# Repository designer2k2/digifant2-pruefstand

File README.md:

# Digifant-2 Prüfstand

Hardware for a fully-automated test bench for the VW Golf 1 Cabrio **Digifant-2** ECU:
signal simulator + capture front-end, driven by a Raspberry Pi Pico 2, with a
high-side load switch so the bench can cold-boot the ECU and cut power on
overcurrent. Scope here is the **Signal-Simulator + Erfassungseinheit** only — the
EPROM emulator is a separate future board.

The schematic is generated from Python with
[circuit-synth](https://github.com/circuit-synth/circuit-synth); the PCB is placed
and autorouted headless (`pcbnew` + Freerouting).

**[`firmware/OPERATION.md`](firmware/OPERATION.md) — how to operate the
bench: display and buttons, PC control and scripting, reading the
measurements.**

**[`BRINGUP.md`](BRINGUP.md) — step-by-step first power-on checklist, tools
needed, and the open questions to settle on the bench.**

**[`DESIGN.md`](DESIGN.md) — what every block does, part-selection rationale, the
GPIO / I²C / VW-harness maps.** [`USE_CASES.md`](USE_CASES.md) traces every real
bench use case through the schematic to concrete numbers (voltage/current/timing
headroom) — a requirements/test matrix for the hardware, and where the AD9833
decoupling-cap gap turned up before it got fixed.

## Layout

| path | what |
|------|------|
| `digifant2_pruefstand.py` | the circuit — one `@circuit` function, flat single sheet |
| `gen_custom_symbols.py` | builds `kicad-symbols/Custom_Digifant2.kicad_sym` (INA226, AD9833, 2N7002, DPAK P-FET, VW connector — pinouts verified against datasheets) |
| `gen_project.py` | `python3 gen_project.py <name>` → full KiCad project + netlist + lib tables, runs ERC/DRC via `kicad-cli`, auto-applies no-connect flags |
| `place_and_route.py` | `pcbnew` functional-zone placement → Specctra DSN → Freerouting → SES import (run inside the KiCad flatpak; `java` runs outside it) |
| `add_nc_flags.py` | stamps `no_connect` flags from an ERC report (circuit-synth has no NC API) |
| `fix_layout.py` | post-route layout surgery (real netclasses, GND/Kelvin re-routing) — see the header comment for the 2-phase, 2-process invocation it needs |
| `reroute_missing.py` | re-exports a Specctra DSN from a partially-ripped-up board so Freerouting only has to fill the reopened ratsnest |
| [`firmware/`](firmware/README.md) | Pico firmware (Pico SDK, C): USB serial command protocol, build/flash instructions, what's implemented vs. stubbed |
| `host/bench.py` | PC-side client for the firmware protocol: interactive prompt, one-shot CLI, or importable `Bench` class; `host/examples/` has a scripted rpm sweep |
| `board/` | the current KiCad project (144×150 mm, 2-layer, 4× M3 corner holes, isolated OLED + USB clearance zones) |
| [`board/bom_output/bom.html`](board/bom_output/bom.html) | interactive BOM ([InteractiveHtmlBom](https://github.com/openscopeproject/InteractiveHtmlBom)) — click a part to highlight it on the board, no KiCad needed |
| [`BOM.md`](BOM.md) | Mouser sourcing: part numbers for every line item, with confidence notes — 6 of 30 need manual confirmation, see the file |
| [`mouser_cart.csv`](mouser_cart.csv) | only the Mouser-verified part numbers, ready to paste into Mouser's bulk order tool |
| [`JLCPCB_ASSEMBLY.md`](JLCPCB_ASSEMBLY.md) | hybrid plan: JLCPCB machine-places the SMD parts, you hand-solder THT + 4 unconfirmed SMD parts — read this before submitting |
| [`jlcpcb_bom.csv`](jlcpcb_bom.csv) / [`jlcpcb_cpl.csv`](jlcpcb_cpl.csv) | JLCPCB SMT-assembly BOM + pick-and-place, 42 of 46 SMD parts (real positions from `board/`, real LCSC part numbers) |
| `UPSTREAM_BUGS.md` | circuit-synth bugs found, drafted for upstream filing |
| `kicad-symbols/`, `kicad-footprints/` | libraries — custom/community committed, stock via `./fetch_libs.sh` |
| `.github/workflows/` | CI: firmware build + tests, spell check, KiCad ERC/DRC, firmware releases (see below) |

## Build

```sh
./fetch_libs.sh                        # one-time: pull stock KiCad 9.0 libs
python3 gen_custom_symbols.py          # if the custom symbols changed
python3 gen_project.py digifant2_pruefstand_cs_v1
```

Placement + routing needs KiCad's `pcbnew` Python API (KiCad ≥ 10) and a
non-headless JRE for Freerouting — see the header of `place_and_route.py`.

## Status

Schematic ERC-clean; VW harness pinout verified against the cabby-info.com
Digifant II reference and the user's own hands-on HiL notes (see `DESIGN.md`).
Board placed + autorouted (144 × 150 mm, 2-layer, 4 × M3 holes, isolated OLED + USB
clearance zones), real Power/Gnd netclasses, GND re-routed as one connected net
(was 4 islands), dedicated Kelvin sense traces for both shunts. The tight
U1/U3/RS1/RS2 pocket (2 shorting_items, 2 clearance, 5 tracks_crossing left by
the scripted Kelvin routing) was cleaned up by hand in KiCad's interactive
router, and a B.Cu GND pour was added. Added the two AD9833 decoupling caps
(C7, C8), fully routed. Fixed RS2 (idle-valve shunt) to be truly in series
with the ECU's VW-23 driver instead of a parallel path to GND that was
corrupting the current reading — this reopened one small pocket at U3 pin 9
(2 `shorting_items`, confined to that one spot after extensive
hand-routing/Freerouting attempts, same class of residual as the historical
U1/U3/RS1/RS2 items). Gave the AD9833 knock output a defined path out
(TP1/TP2 test points for VW-4/VW-5) instead of a dead end. Added 12 more
THT scope-probe test points (TP3–TP14, real drilled holes — an earlier pass
used bare SMD pads and put 10 of them physically underneath the Pico module,
both corrected) on the main GPIO signals, both buses, and both 12 V rails.
Found and fixed a real bug along the way: footprints cloned via
`pcbnew.FOOTPRINT(template)` inherit the template's UUID unless you
explicitly reset it, which had corrupted DRC's item-identity tracking for
every cloned part this session (C7/C8 and all of TP1–TP14) — several
"violations" turned out to be real defects reported against the wrong
footprint. See DESIGN.md's "Known open points" for details if you script
further additions. Remaining warnings are cosmetic (silkscreen overlap,
lib_footprint_mismatch, and one starved_thermal note on a single Pico GND
pad with only 1 pour spoke instead of 2 — connected fine, just a slightly
weaker thermal/mechanical joint). Thermal copper for D1/Q2 still optional to
add by hand. Added a 12×16 perfboard-style proto area (PROTO1, isolated THT
pads on 0.1″ pitch) in the empty space bottom-right of J0. Checked the whole
board against JLCPCB's published fab minimums (trace/spacing, via/hole sizes,
hole-to-hole, copper-to-edge, board thickness) — everything copper- and
hole-related had 1.5×–14× margin already. The one real miss was silkscreen:
KiCad's default 0.1mm line width and 0.8mm text height are both below
JLCPCB's stated minimums (0.15mm / 1.0mm), risking thin/dropped silkscreen.
Bumped the project defaults and widened/enlarged every existing silkscreen
line and text item on the board to meet those minimums.

Checked +3V3 for adequate trace width (it's on the thinnest `Default`
netclass, 0.2mm, despite feeding ~15 chips) — worked out the real numbers
(thermal capacity ~0.77A at 10°C rise, worst-case drop a few mV) and it's
fine as-is; not worth the rerouting risk in this densely-packed board.
Checked decoupling instead: per each part's own datasheet, U1 and U3 (the
two INA226 current-sense amps) had no bypass cap at all, unlike U2/U4 which
already have theirs (C6, C2/C7/C8). Added C9 (U1) and C10 (U3), 100nF 0805,
tapped directly off the existing +3V3 B.Cu trunk and the GND pour a few mm
south of the packed U1/U3/RS1/RS2 pocket (no room to place them right at the
pins) — verified DRC-clean (the only residuals are the same
new-copper-vs-stale-zone-fill noise that clears on a zone refill, same as
after the TP resort). U6/U7/U8 (the sensor-disconnect analog switches) are
still without a bypass cap; lower priority since they're not
noise-sensitive, but could use the same treatment.

Added the thermal copper for D1/Q2 that was flagged as a real (not
cosmetic) risk in USE_CASES.md — D1 dissipates ~1.25W at sustained ~2.5A
with no thermal relief otherwise. Both pours verified electrically
connected to their pads (not just overlapping) and DRC-clean. Q2's is
small since there's almost no open board space around its DPAK tab; D1's
is generous since F1/RS1 (same nets, either side) leave a wide open
corridor.

**All 14 test points (TP1–TP14) are now fully routed** — the user hand-routed
7 of the 10 remaining GPIO test points after the resort (TP3, TP10, TP11,
TP4, TP12, TP5, TP6); the last 3 (TP9, TP8, TP7 — all on U5's east side, the
tightest part of the board) were routed with a grid-based pathfinder (A* over
a 0.1mm grid, spatial-bucket-indexed for speed) purpose-built for this corridor
after several rounds of manual/heuristic routing kept snagging on real
obstacles: the Pico's own pin column has no gap wide enough for a second
trace anywhere along its length (confirmed by direct probing — routed escape
stubs from other GPIOs fill in what would otherwise be a 0.49mm theoretical
gap between pin pads), so both TP8 and TP9 had to detour around the *south*
end of the Pico footprint entirely, and — since that detour corridor is
itself only wide enough for one trace at a time — needed genuinely different
physical crossing points, not just parallel lanes. Verified via real
`kicad-cli pcb drc`, not just the pathfinder's own clearance model (which
undercounted real collisions during development in two ways worth noting for
next time: it modeled non-circular pads by their half-width instead of their
half-diagonal, and it didn't check hole-to-hole spacing against a net's own
via near its own pad — both are now fixed in the approach, see `DESIGN.md`).
GND zone refilled after all of the above (TP9/TP8 routing, C9/C10, D1/Q2
thermal pours) — DRC dropped from 136 to 101 violations, all pre-existing
cosmetic categories plus the one known `starved_thermal` note, zero
clearance/short/crossing issues. (The "whole-board refill introduces ~115
spurious violations" finding earlier this session was a testing artifact —
running `kicad-cli` against a bare copy of the `.kicad_pcb` without its
paired `.kicad_pro` silently falls back to stricter default netclass rules;
with the project file present, the refill is clean.)

Trimmed the board from 144×169mm to 144×150mm — the bottom 19mm was
completely empty (bare GND pour, nothing below PROTO1/J3 until the old
mounting holes). H3/H4 moved up to keep the same 4.5mm hole-to-edge margin
as H1/H2; DRC stayed clean (99 violations, same pre-existing cosmetic set).

Added functional silkscreen labels next to J0 (the VW harness connector) and
every test point, instead of leaving bare unlabeled pads. J0 gets each pin's
real VW harness number (VW-2, VW-9, ... or GND / +12V SW) in the clear strip
just outside its footprint. The TPs already had descriptive text (e.g.
`GP2_CRANK`) sitting on them from earlier in the session — turned out it was
on **F.Fab**, a documentation-only layer that doesn't actually get printed on
the physical board, so none of it was ever going to be visible with a probe
in hand. Moved it to F.SilkS and shortened the long ones (e.g.
`GP6_THROTTLE_IDLE_SW` → `IDLE SW`) since the west-margin TP column only has
about 10mm of clearance between the board edge and the Pico's pin column —
the original full-length strings would have run off the board edge once
actually rendered as real silkscreen (checked via real bounding-box widths,
not by eye). This did add some new `silk_overlap` hits — mostly TP labels
sitting close to the Pico module's own tiny per-pin silkscreen text in that
same tight corridor — all cosmetic, same accepted category as the rest of
this board's silkscreen warnings, verified via DRC to introduce zero
clearance/short/crossing issues.

Added fab-identification text on the back silkscreen (B.SilkS, previously
completely empty — no back components, nothing on that layer at all):
project name, revision, date, and designer, so a bare board can still be
identified later. Set via the board's title block (`${TITLE}`,
`${REVISION}`, `${ISSUE_DATE}`, `${COMPANY}`) rather than hardcoded text, so
updating the revision/date for a future respin is a one-place edit in
KiCad's Page Settings, not a silkscreen re-edit. Verified the variables
resolve correctly (checked the exported SVG's embedded text, since this
sandbox can't render the actual glyphs) and confirmed zero new DRC
violations. Not yet fabbed.

## Continuous integration

Every push and pull request runs on GitHub Actions:

| Workflow | What it checks |
|---|---|
| **CI** (`ci.yml`) | Builds the firmware with Pico SDK 2.1.1, warnings as errors, and uploads `pruefstand.uf2` as a build artifact. Runs `firmware/test/run_all.sh`: all PC unit tests, the command parser, `host/bench.py` over a virtual serial port, and the crank PIO program in an emulator. |
| | Spell check with [codespell](https://github.com/codespell-project/codespell) over code, comments and docs (`.codespellrc`). |
| **Board** (`board.yml`, only when `board/` changes) | KiCad 10 ERC, and DRC with schematic parity. Fails on errors (unconnected nets, clearance, shorts); the known cosmetic warnings are only reported. Full reports are attached to the run. |

Before opening a pull request, the same checks run locally with
`firmware/test/run_all.sh` (after a firmware build) and `codespell`.

**Firmware releases:** bump `FW_VERSION` in `firmware/src/cmd.h`, commit, then
push a matching tag, e.g. `git tag fw-v0.9.0 && git push origin fw-v0.9.0`. CI
checks the tag against `FW_VERSION`, runs everything above, and publishes a
GitHub Release with `pruefstand-<version>.uf2` to download and flash.

## License

MIT (see `LICENSE`) for everything authored here — scripts, custom symbols, the
board design. Bundled third-party files (the Raspberry Pi Pico symbol/footprint
from [ncarandini/KiCad-RP-Pico](https://github.com/ncarandini/KiCad-RP-Pico),
CC-BY-SA-4.0) keep their own licenses — see `NOTICE`.

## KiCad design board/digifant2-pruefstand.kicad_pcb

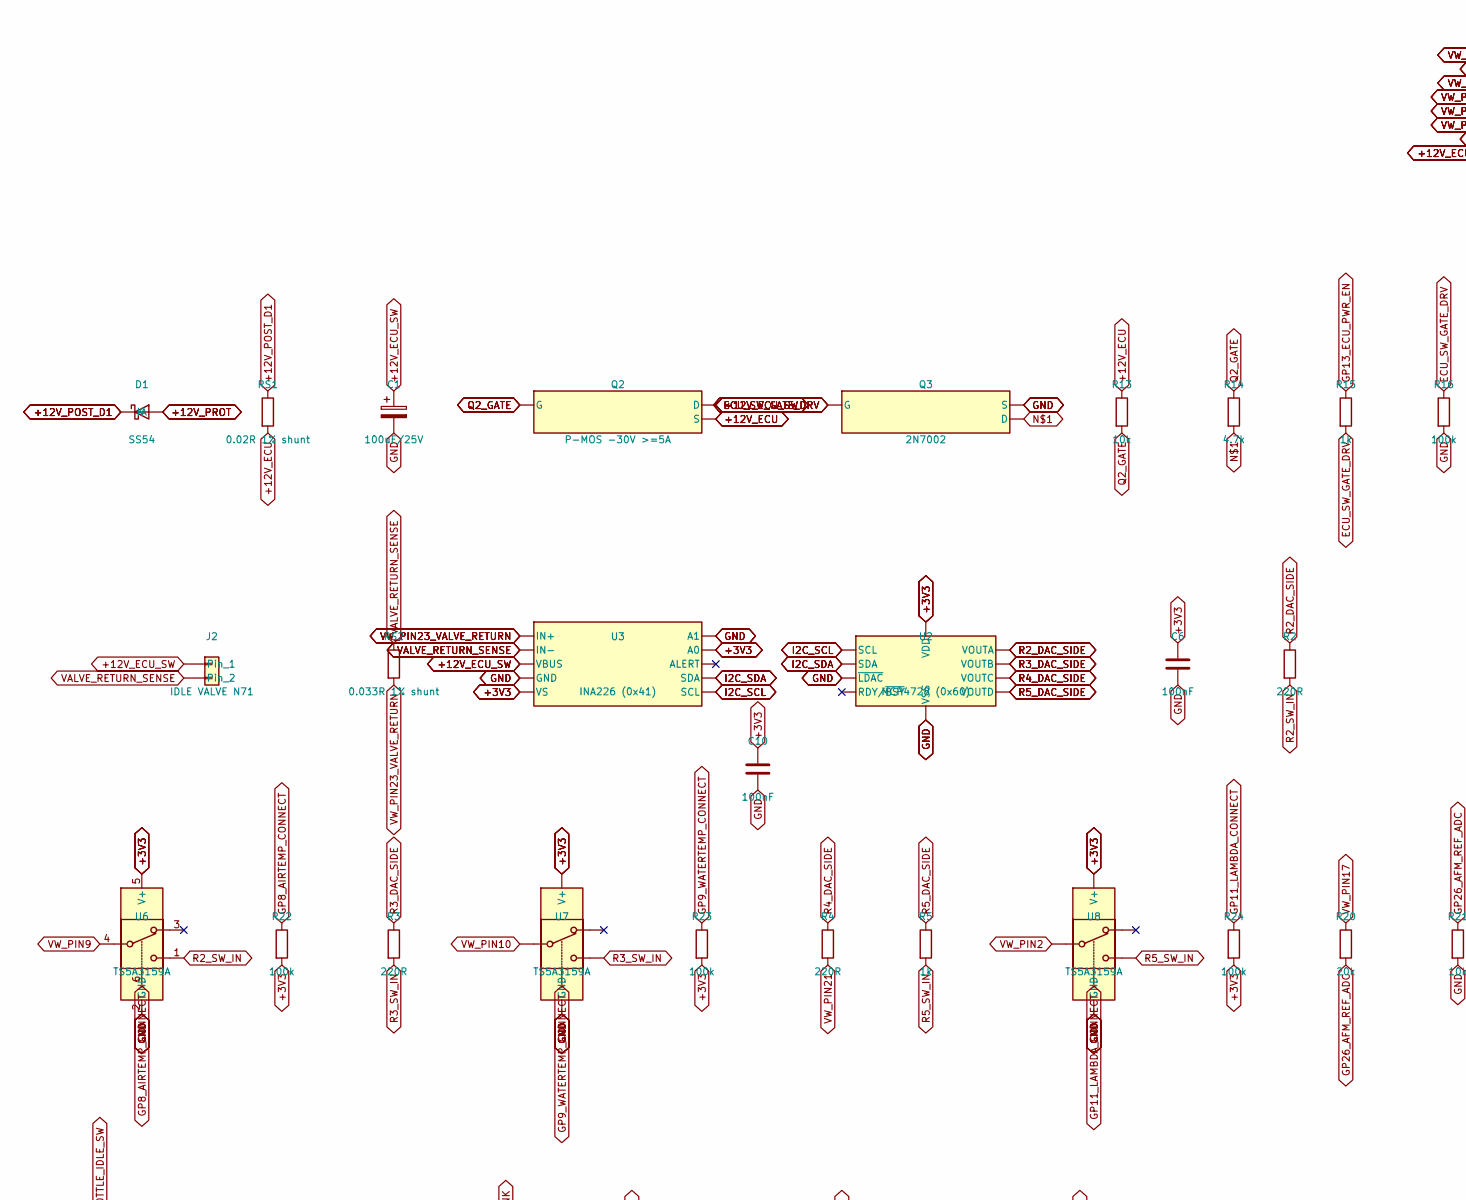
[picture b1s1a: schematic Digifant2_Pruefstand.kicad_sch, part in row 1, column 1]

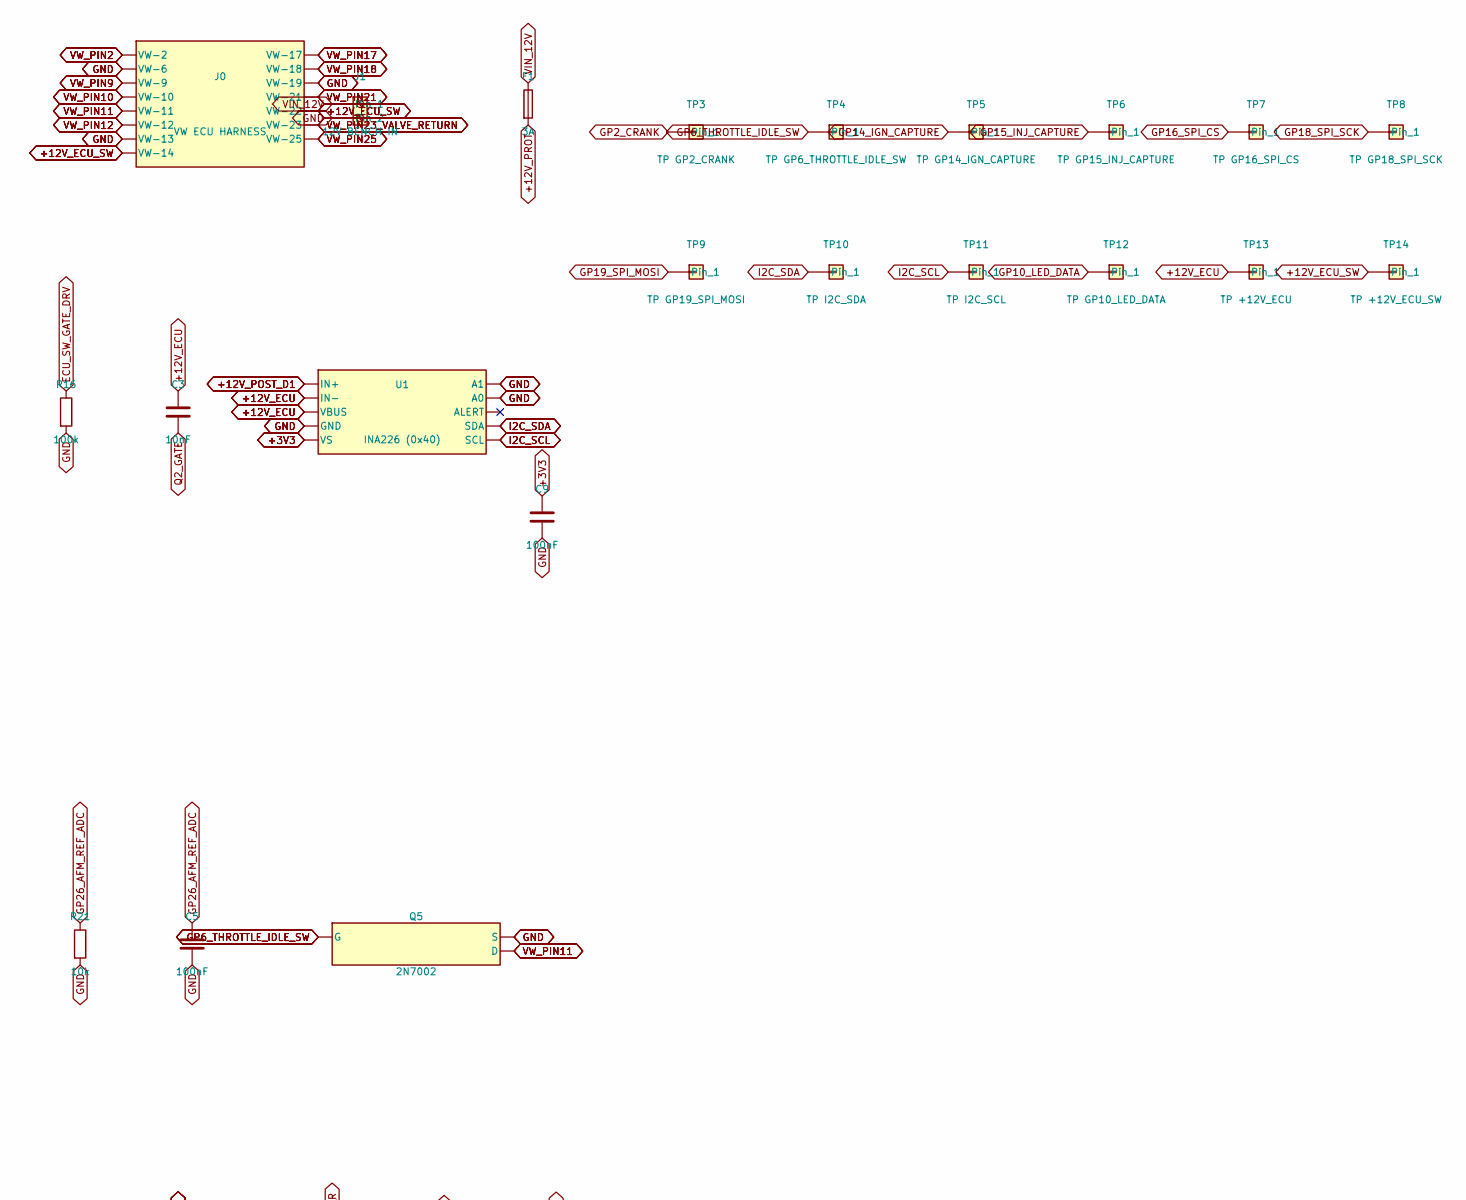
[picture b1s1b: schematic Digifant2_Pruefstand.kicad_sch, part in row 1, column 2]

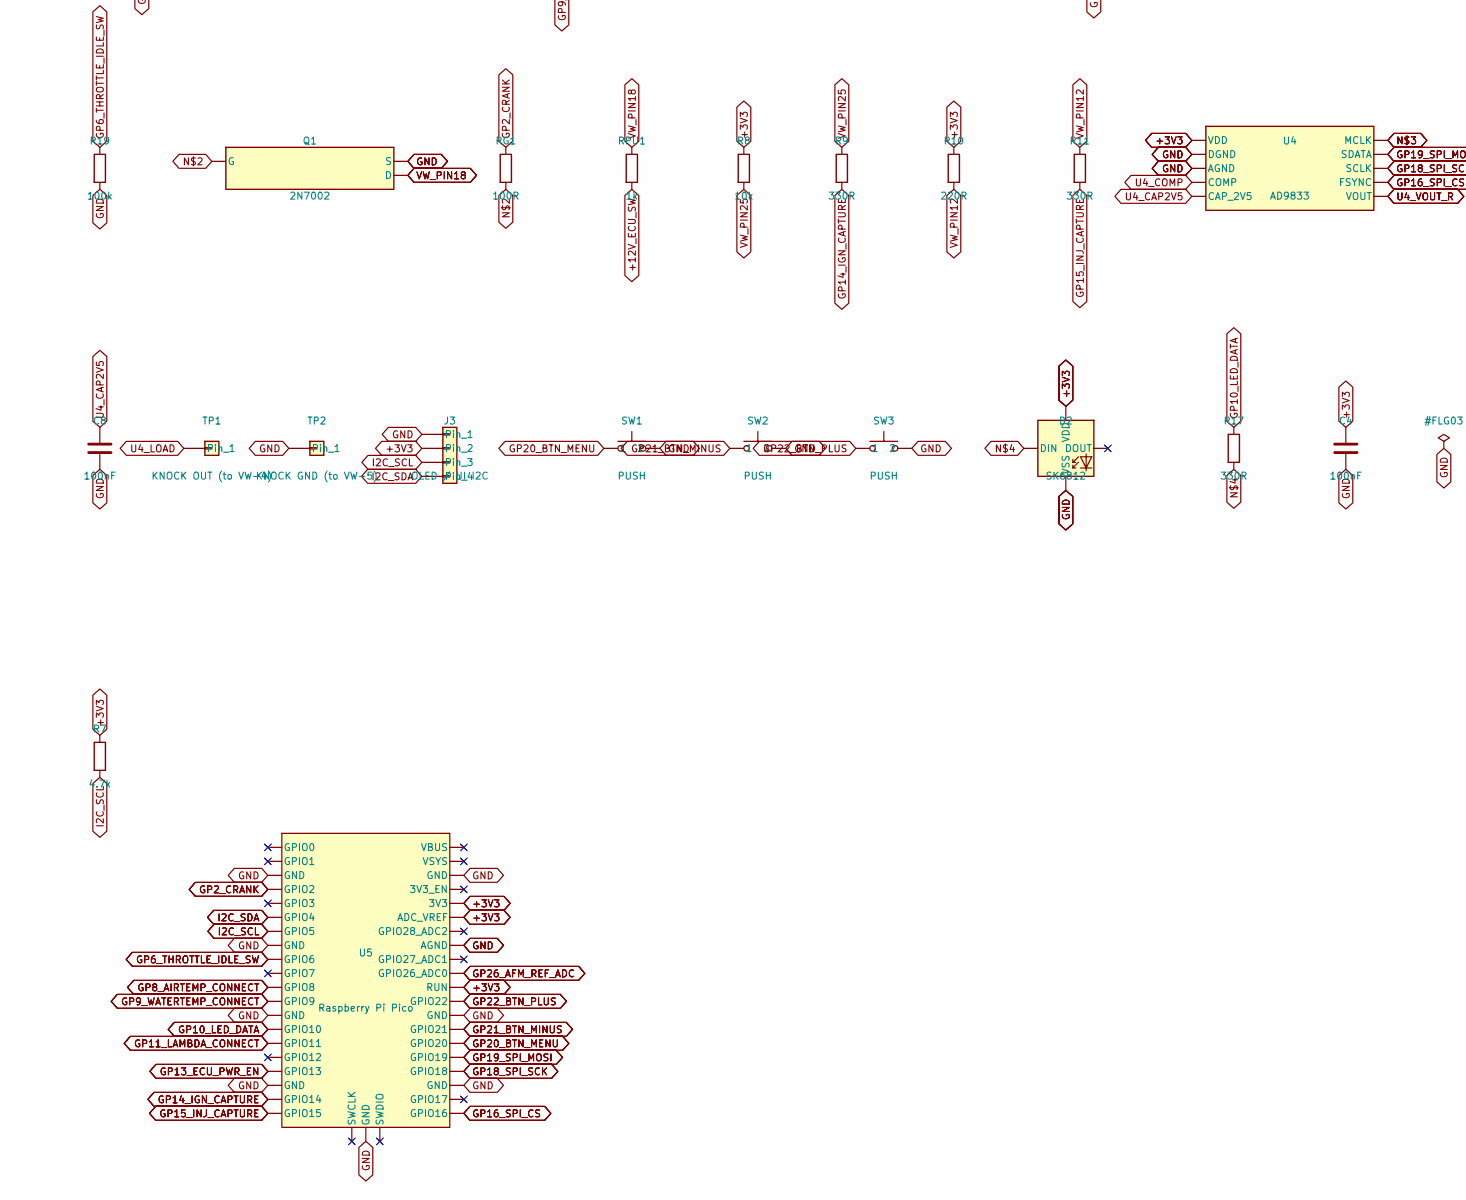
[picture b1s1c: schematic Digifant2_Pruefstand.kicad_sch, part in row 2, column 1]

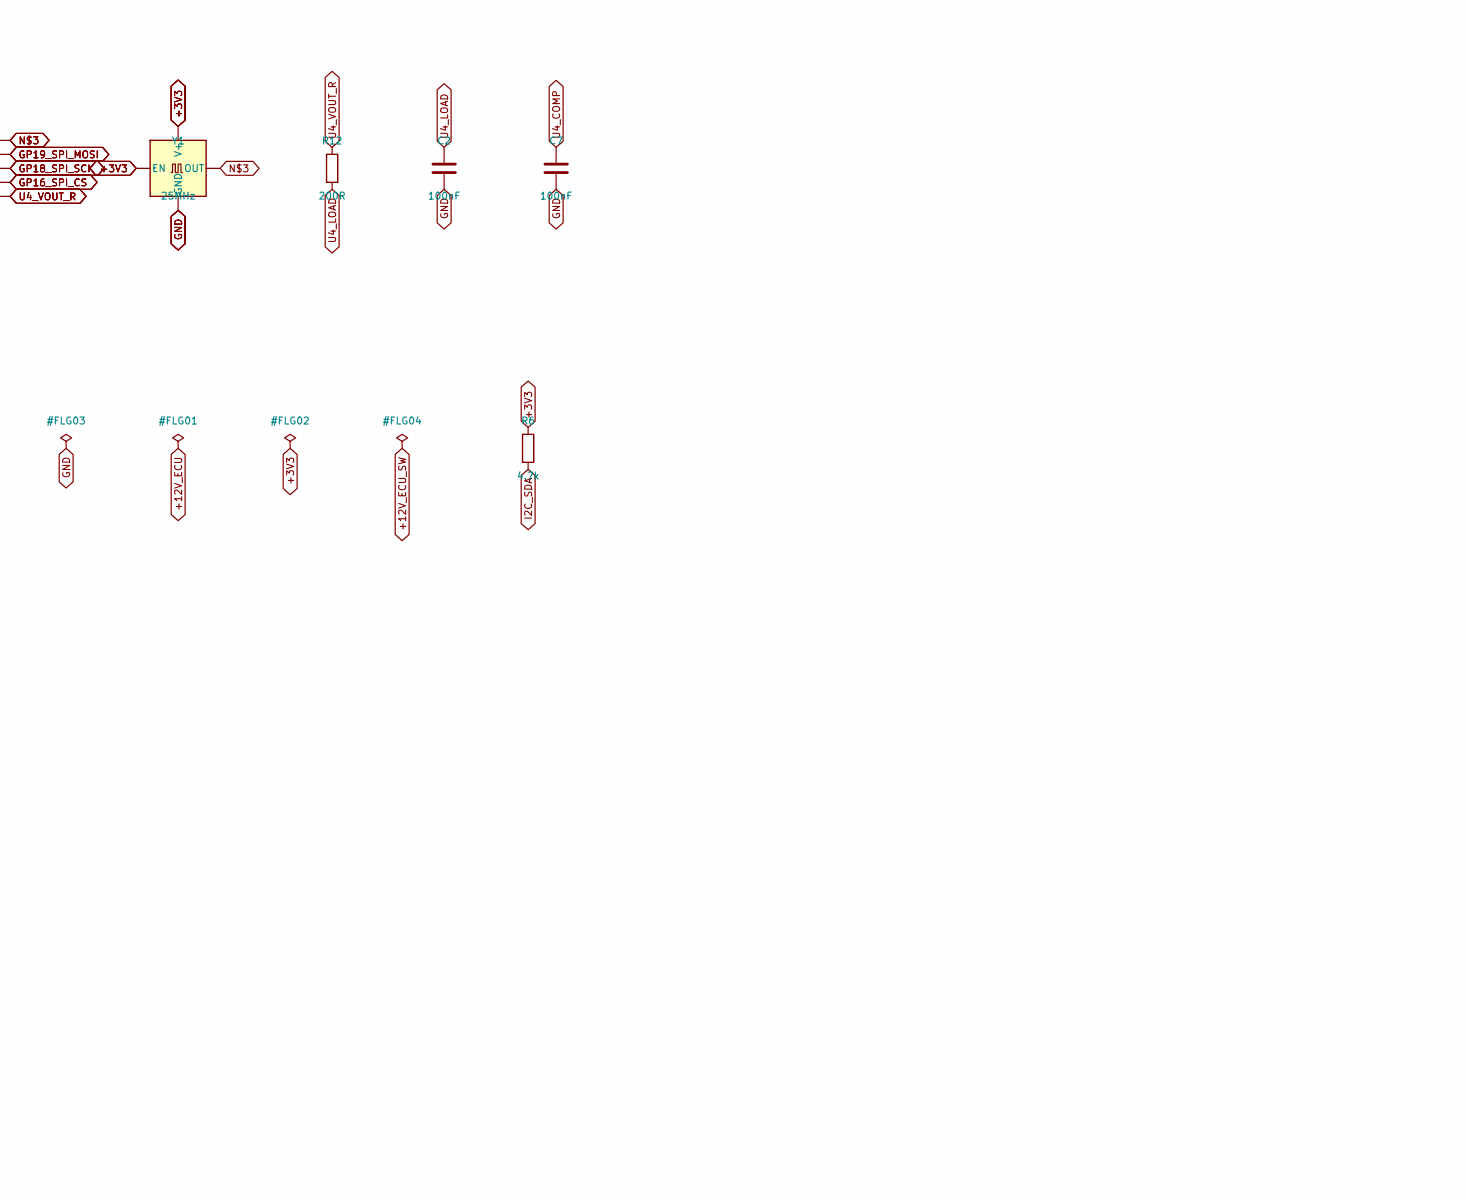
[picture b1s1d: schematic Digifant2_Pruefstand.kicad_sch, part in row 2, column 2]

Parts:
C1: 100uF/25V; CP_Radial_D8.0mm_P3.50mm
C2, C4, C5, C6, C7, C8, C9, C10: 100nF; C_0805_2012Metric
C3: 10nF; C_0805_2012Metric
D1: SS54; D_SMC
D2: SK6812; LED_SK6812_PLCC4_5.0x5.0mm_P3.2mm
F1: 3A; Fuse_1206_3216Metric
J0: VW ECU HARNESS; TerminalBlock_MaiXu_MX126-5.0-15P_1x15_P5.00mm
J1: 12V BENCH IN; TerminalBlock_bornier-2_P5.08mm
J2: IDLE VALVE N71; JST_XH_B2B-XH-A_1x02_P2.50mm_Vertical
J3: OLED / UI I2C; PinHeader_1x04_P2.54mm_Vertical
Q1, Q3, Q5: 2N7002; SOT-23
Q2: P-MOS -30V >=5A; TO-252-2
R2, R3, R4, R10: 220R; R_0805_2012Metric
R5, R15: 1k; R_0805_2012Metric
R6, R7, R14: 4.7k; R_0805_2012Metric
R8, R13, R21: 10k; R_0805_2012Metric
R9, R11, R17: 330R; R_0805_2012Metric
R12: 200R; R_0805_2012Metric
R16, R19, R22, R23, R24: 100k; R_0805_2012Metric
R20: 20k; R_0805_2012Metric
RG1: 100R; R_0805_2012Metric
RPU1: 1k; R_0805_2012Metric
RS1: 0.02R 1% shunt; R_2512_6332Metric
RS2: 0.033R 1% shunt; R_2512_6332Metric
SW1, SW2, SW3: PUSH; SW_PUSH_6mm
TP1: KNOCK OUT (to VW-4); TestPoint_THTPad_D1.5mm_Drill0.7mm
TP2: KNOCK GND (to VW-5); TestPoint_THTPad_D1.5mm_Drill0.7mm
TP3: TP GP2_CRANK; TestPoint_THTPad_D1.5mm_Drill0.7mm
TP4: TP GP6_THROTTLE_IDLE_SW; TestPoint_THTPad_D1.5mm_Drill0.7mm
TP5: TP GP14_IGN_CAPTURE; TestPoint_THTPad_D1.5mm_Drill0.7mm
TP6: TP GP15_INJ_CAPTURE; TestPoint_THTPad_D1.5mm_Drill0.7mm
TP7: TP GP16_SPI_CS; TestPoint_THTPad_D1.5mm_Drill0.7mm
TP8: TP GP18_SPI_SCK; TestPoint_THTPad_D1.5mm_Drill0.7mm
TP9: TP GP19_SPI_MOSI; TestPoint_THTPad_D1.5mm_Drill0.7mm
TP10: TP I2C_SDA; TestPoint_THTPad_D1.5mm_Drill0.7mm
TP11: TP I2C_SCL; TestPoint_THTPad_D1.5mm_Drill0.7mm
TP12: TP GP10_LED_DATA; TestPoint_THTPad_D1.5mm_Drill0.7mm
TP13: TP +12V_ECU; TestPoint_THTPad_D1.5mm_Drill0.7mm
TP14: TP +12V_ECU_SW; TestPoint_THTPad_D1.5mm_Drill0.7mm
U1: INA226 (0x40); MSOP-10_3x3mm_P0.5mm
U2: MCP4728 (0x60); MSOP-10_3x3mm_P0.5mm
U3: INA226 (0x41); MSOP-10_3x3mm_P0.5mm
U4: AD9833; MSOP-10_3x3mm_P0.5mm
U5: Raspberry Pi Pico; RPi_Pico_SMD_TH
U6, U7, U8: TS5A3159A; SOT-23-6
Y1: 25MHz; Oscillator_SMD_EuroQuartz_XO91-4Pin_7.0x5.0mm

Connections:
+12V_ECU: C3.1, Q2.3 (S), R13.1, RS1.2, TP13.1, U1.8 (VBUS), U1.9 (IN-)
+12V_ECU_SW: C1.1, J0.8 (VW-14), J0.13 (VW-22), J2.1, Q2.2 (D), RPU1.2, TP14.1, U3.8 (VBUS)
+12V_POST_D1: D1.1 (K), RS1.1, U1.10 (IN+)
+12V_PROT: D1.2 (A), F1.2
ECU_SW_GATE_DRV: Q3.1 (G), R15.2, R16.1
GP2_CRANK: RG1.1, TP3.1, U5.4 (GPIO2)
GP6_THROTTLE_IDLE_SW: Q5.1 (G), R19.1, TP4.1, U5.9 (GPIO6)
GP8_AIRTEMP_CONNECT: R22.1, U5.11 (GPIO8), U6.6
GP9_WATERTEMP_CONNECT: R23.1, U5.12 (GPIO9), U7.6
GP10_LED_DATA: R17.1, TP12.1, U5.14 (GPIO10)
GP11_LAMBDA_CONNECT: R24.1, U5.15 (GPIO11), U8.6
GP13_ECU_PWR_EN: R15.1, U5.17 (GPIO13)
GP14_IGN_CAPTURE: R9.2, TP5.1, U5.19 (GPIO14)
GP15_INJ_CAPTURE: R11.2, TP6.1, U5.20 (GPIO15)
GP16_SPI_CS: TP7.1, U4.8 (FSYNC), U5.21 (GPIO16)
GP18_SPI_SCK: TP8.1, U4.7 (SCLK), U5.24 (GPIO18)
GP19_SPI_MOSI: TP9.1, U4.6 (SDATA), U5.25 (GPIO19)
GP20_BTN_MENU: SW1.1, U5.26 (GPIO20)
GP21_BTN_MINUS: SW2.1, U5.27 (GPIO21)
GP22_BTN_PLUS: SW3.1, U5.29 (GPIO22)
GP26_AFM_REF_ADC: C5.1, R20.2, R21.1, U5.31 (GPIO26_ADC0)
I2C_SCL: J3.3, R7.2, TP11.1, U1.5 (SCL), U2.2 (SCL), U3.5 (SCL), U5.7 (GPIO5)
I2C_SDA: J3.4, R6.2, TP10.1, U1.4 (SDA), U2.3 (SDA), U3.4 (SDA), U5.6 (GPIO4)
unnamed: Q3.3 (D), R14.2
unnamed: Q1.1 (G), RG1.2
unnamed: U4.5 (MCLK), Y1.3 (OUT)
unnamed: D2.2 (DIN), R17.2
Q2_GATE: C3.2, Q2.1 (G), R13.2, R14.1
R2_DAC_SIDE: R2.1, U2.6 (VOUTA)
R2_SW_IN: R2.2, U6.1
R3_DAC_SIDE: R3.1, U2.7 (VOUTB)
R3_SW_IN: R3.2, U7.1
R4_DAC_SIDE: R4.1, U2.8 (VOUTC)
R5_DAC_SIDE: R5.1, U2.9 (VOUTD)
R5_SW_IN: R5.2, U8.1
U4_CAP2V5: C8.1, U4.3 (CAP_2V5)
U4_COMP: C7.1, U4.1 (COMP)
U4_LOAD: C2.1, R12.2, TP1.1
U4_VOUT_R: R12.1, U4.10 (VOUT)
VALVE_RETURN_SENSE: J2.2, RS2.1, U3.9 (IN-)
VIN_12V: F1.1, J1.1
VW_PIN2: J0.1 (VW-2), U8.4
VW_PIN9: J0.3 (VW-9), U6.4
VW_PIN10: J0.4 (VW-10), U7.4
VW_PIN11: J0.5 (VW-11), Q5.3 (D)
VW_PIN12: J0.6 (VW-12), R10.2, R11.1
VW_PIN17: J0.9 (VW-17), R20.1
VW_PIN18: J0.10 (VW-18), Q1.3 (D), RPU1.1
VW_PIN21: J0.12 (VW-21), R4.2
VW_PIN23_VALVE_RETURN: J0.14 (VW-23), RS2.2, U3.10 (IN+)
VW_PIN25: J0.15 (VW-25), R8.2, R9.1

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
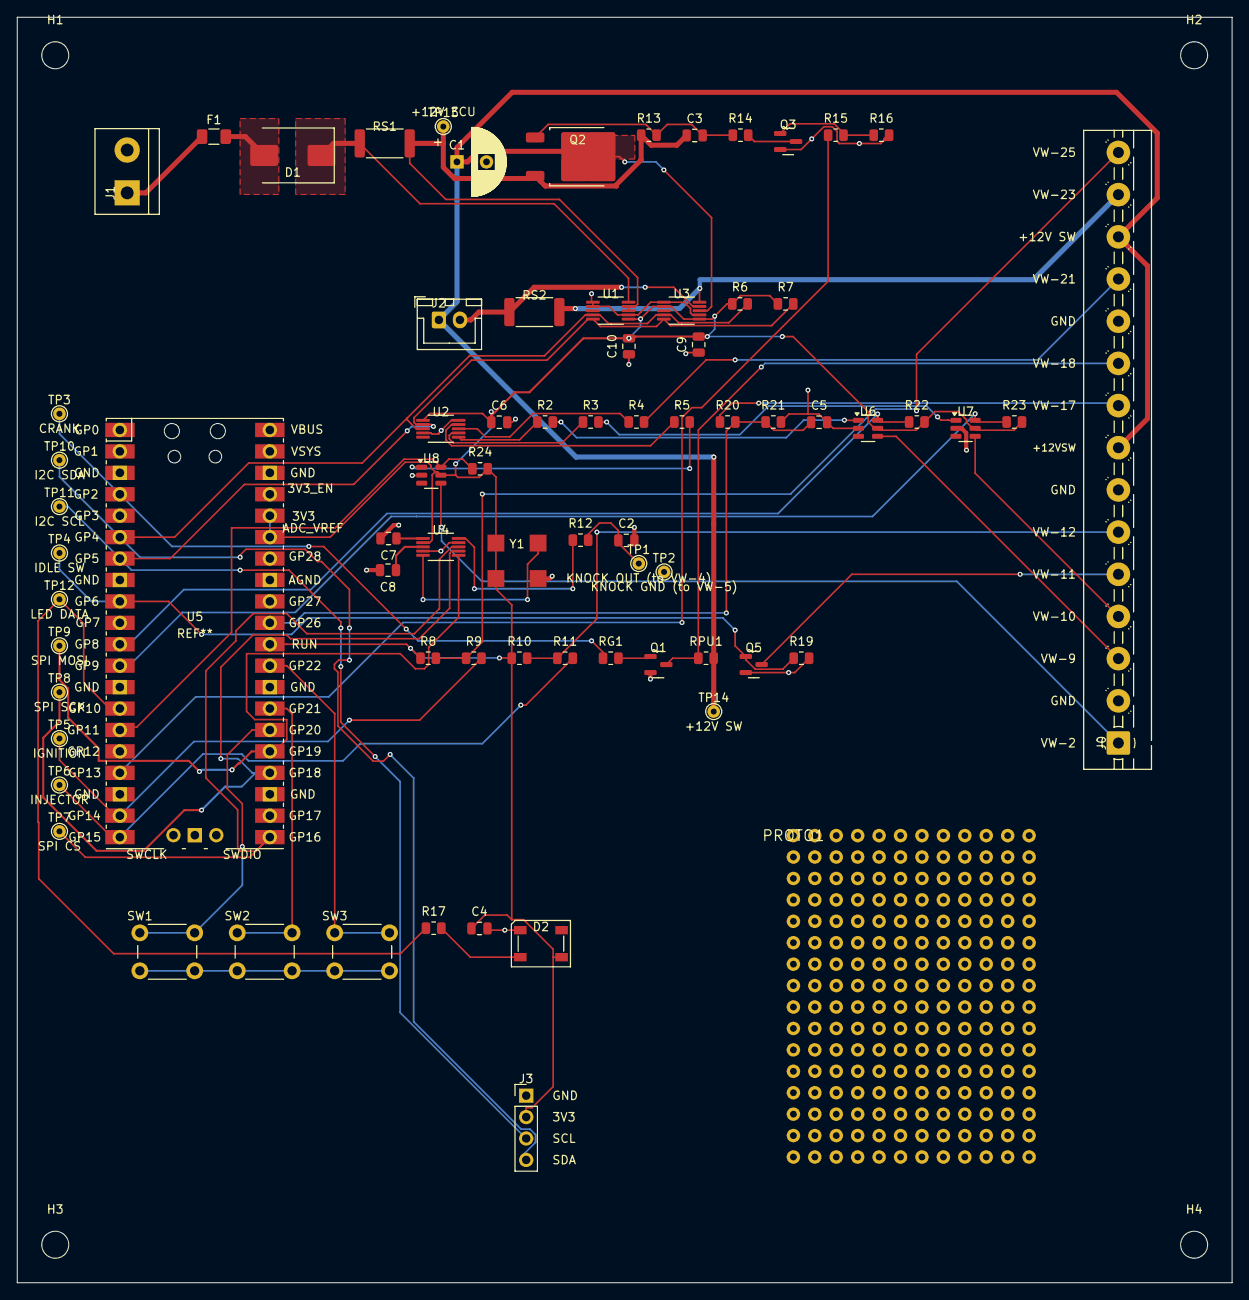
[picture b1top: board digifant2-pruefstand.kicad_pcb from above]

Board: 2 copper layers, 144.0 x 150.0 mm, 78 parts (0 on the bottom side), 53 nets.

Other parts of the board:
H1, H2, H3, H4: MountingHole_3.2mm_M3
PROTO1: PROTO AREA

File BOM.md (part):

# Bill of Materials — Mouser sourcing

Researched against mouser.com (2026-09-12). **Confidence matters here — read it per row.**
"Verified" means an actual Mouser product page was found for that exact part.
"Pattern-matched" means it's the same manufacturer part-numbering family as a
verified sibling value (e.g. Yageo's `RC0805FR-07<value>L` resistors — five
other values in this exact series were independently verified on Mouser, so
the same convention for these mid-values is reliable but wasn't individually
page-confirmed). "Could not confirm" means: **do not order this part number —
it may not exist.** Search Mouser yourself or use an alternate distributor.

Also see [`board/bom_output/bom.html`](board/bom_output/bom.html) for the
interactive per-footprint BOM (no Mouser data, but useful to see where each
part sits on the board).

**2026-10-08, cross-checked against a real assembly report:** `mouser_cart.csv`
(the actual order file) had never included R9/R11/R17 (330Ω), R12 (200Ω) or
RG1 (100Ω) — present in this table since the start, but missed when the cart
was built, so they were never actually ordered. Fixed now; order these five
separately if you've already placed the original cart. U1/U3 (qty 2 INA226)
and U4 (AD9833) are, and have been since the 2026-09-20 correction pass,
correct in `mouser_cart.csv` — if your kit is short on these, the order was
likely placed from an older snapshot; check your own Mouser order history
against the current file rather than re-ordering blind.

| Ref(s) | Qty | Description | Mfr / Mfr P/N | Mouser P/N | Confidence |
|---|---|---|---|---|---|
| U5 | 1 | Raspberry Pi Pico 2 (RP2350, THT/castellated) | Raspberry Pi / SC1631 | [SC1631](https://www.mouser.com/en/ProductDetail/Raspberry-Pi/SC1631) | Mfr P/N confirmed against Digikey's listing (SC1631 = plain Pico 2, no wireless -- SC1632/3/4 are the H/W/WH variants); Mouser's own page timed out twice when checked automatically, so check it live before ordering. **The originally-ordered SC0915 (RP2040 Pico) is not used here anymore -- it's now a spare, a Pico 2 needs to be ordered separately.** |
| U1, U3 | 2 | INA226 current/power monitor, MSOP-10 | TI / INA226AIDGST | [INA226AIDGST](https://www.mouser.com/en/ProductDetail/Texas-Instruments/IN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 | Swapped to the `T` suffix (small reel, ~250 units) instead of `R` (standard reel, ~2500) — same die/package/pinout, just a smaller reel size that makes more sense for a qty-2 order. **RS Components alternative: RS 742-2889**, confirmed across several regional RS sites. |
| U2 | 1 | MCP4728 quad 12-bit DAC, MSOP-10 | Microchip / MCP4728-E/UN | [MCP4728-E-UN](https://www.mouser.com/ProductDetail/Microchip-Technology/MC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 | Verified |
| U4 | 1 | AD9833 DDS waveform generator, MSOP-10 | Analog Devices / AD9833BRMZ-REEL7 | [AD9833BRMZ-REEL7](https://www.mouser.com/en/ProductDetail/Analog-Devices/AD983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 | Corrected by the user while ordering — plain AD9833BRMZ isn't orderable, needs the -REEL7 tape-and-reel suffix (same die, just packaging). **RS Components alternative: RS 183-2180** — RS sells the plain `AD9833BRMZ` (no reel suffix needed), confirmed at £10.84/unit (UK). |
| U6, U7, U8 | 3 | TS5A3159A SPDT analog switch, SOT-23-6 | TI / TS5A3159ADBVR | [TS5A3159ADBVR](https://www.mouser.com/ProductDetail/Texas-Instruments/TS5A3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 | Verified — **but flagged as possibly EOL at TI in search results; confirm current lifecycle/stock before ordering qty 3** |
| RS1 | 1 | 0.02Ω 1% current-sense shunt, 2512 | Bourns / CRA2512-FZ-R020ELF | [CRA2512-FZ-R020ELF](https://www.mouser.com/ProductDetail/Bourns/CRA2512-FZ-R020ELF) | Verified |
| RS2 | 1 | 0.033Ω 1% current-sense shunt, 2512 | Vishay Dale / WSL2512R0330FEA | [71-WSL2512R0330FEA](https://www.mouser.com/ProductDetail/Vishay-Dale/WSL2512R0330FEA) | Found by the user — the originally-listed Bourns `CRA2512-FZ-R033ELF` exists on Mouser (652-) but shows 0 stock; this Vishay WSL2512 part is the same value/package and in stock. |
| Q2 | 1 | P-channel MOSFET, DPAK, ≤-30V, ≥5A (ECU high-side switch) | Vishay / SUD50P06-15-GE3 | [SUD50P06-15-GE3](https://www.mouser.com/ProductDetail/Vishay-Semiconductors/S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 | Verified — spec is well over-built (-60V/-50A) for a real, exact-package match; fine to use, or substitute a tighter-spec DPAK P-FET if you prefer |
| Q1, Q3, Q5 | 3 | 2N7002 N-MOSFET, SOT-23 | onsemi / 2N7002 | [512-2N7002](https://www.mouser.com/ProductDetail/onsemi/2N7002) | Found by the user on Mouser |
| D1 | 1 | SS54 Schottky diode, SMC/DO-214AB, 5A/40V | Diodes Inc. / SS54FSH | [821-SS54FSH](https://www.mouser.com/ProductDetail/Diodes-Incorporated/SS54FSH) | Found by the user on Mouser — Diodes Inc.'s SS54 in the same SMC package, confirms the originally-listed Comchip part just wasn't the right distributor. |
| D2 | 1 | SK6812 addressable RGB LED, PLCC-4, 5.0×5.0mm, P3.2mm pad pitch | OPSCO / SK6812 | [LCSC C5378720](https://www.lcsc.com/product-detail/C5378720.html) | **Confirmed: not stocked on Mouser.** Best lead found: OPSCO's plain SK6812 (not RGBW) on LCSC, C5378720, 4-pin SMD-4P, in stock. Its listed body is 5.4×5.0mm vs our footprint's 5.0×5.0mm — **verify the 3.2mm pad pitch against its datasheet before ordering**; PLCC-4 SK6812 clones commonly share pad pitch despite small body differences, but this wasn't independently confirmed. Also usable: AliExpress or Adafruit (search "SK6812 5050 RGB") — **not** SK6812MINI/MINI-E (3.5mm) or 2020/EC (2mm), which don't fit the footprint, and **not** RGBW (fits mechanically, but is a 32-bit-per-pixel format the firmware would need to handle — Adafruit's own SK6812 boards are RGBW). WS2812B 5050 is the usual drop-in fallback if SK6812 can't be sourced — check pin 1 against its datasheet before soldering. Note: D2 runs from +3V3, below the typical SK6812 VDD spec (~3.5–5.3V); usually still works, blue/green may be dimmer. **RS Components does not have a usable match: their own SK6812 (RS 1808086) is a 3535 package, confirmed too small for this 5050/PLCC-4 footprint.** |
| F1 | 1 | 3A fuse, 1206/3216 SMD | Bel Fuse / TR/3216FF3-R | [504-TR/3216FF3-R](https://www.mouser.com/ProductDetail/Bel-Fuse/TR-3216FF3-R) | Found by the user on Mouser — Bel's naming embeds the rating (FF3 = 3A fast-acting) |
| C1 | 1 | 100µF/25V radial electrolytic, 8mm dia., 3.5mm pitch | Panasonic / ESH107M035AG3AA | [80-ESH107M035AG3AA](https://www.mouser.com/ProductDetail/Panasonic/ESH107M035AG3AA) | Found by the user on Mouser — decodes to 100µF/35V (not 25V as designed, but higher voltage rating is a safe substitute, pure margin upgrade) |
| J1 | 1 | 2-pos 5.08mm PCB screw terminal, THT | Phoenix Contact / 1935161 | [1935161](https://www.mouser.com/ProductDetail/Phoenix-Contact/1935161) | Best match, not exact — this Phoenix part is a **fixed** 5.00mm block; the board footprint (`TerminalBlock_bornier-2_P5.08mm`) implies pluggable. Mechanically close (0.08mm off pitch), functionally fine, but check fit before ordering many. |
| J0 | 1 | 15-pos 5.00mm screw terminal, THT | Molex / 39543-0015 | [39543-0015](https://www.mouser.com/ProductDetail/Molex/39543-0015) | Found by the user on Mouser — confirmed 15 positions / 5.00mm pitch (matches the `MX126-5.0-15P` footprint exactly). Not confirmed pluggable vs. fixed one-piece style; either works mechanically/electrically, fixed just loses the unplug-the-whole-harness convenience. |
| J2 | 1 | JST XH 2-pos, 2.50mm pitch, vertical THT header | JST / B2B-XH-A(LF)(SN) | [B2B-XH-ALFSN](https://www.mouser.com/ProductDetail/JST-Commercial/B2B-XH-ALFSN) | Verified — two very similar part numbers turned up (`B2B-XH-ALFSN` and `B2B-XH-2LFSN`); double-check the page shows 2-position before ordering |
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
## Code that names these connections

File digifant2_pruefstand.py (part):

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    c10[2] += gnd


def afm_ref_sense(vw_pin17, gnd, adc):
    """The airflow-meter potentiometer is read ratiometrically: the ECU sources a
    reference on VW-17 and reads the wiper on VW-21. We inject the wiper voltage
    with the DAC, so firmware needs to know VW-17's actual level to scale it (and
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    r20 = Component("Device:R", ref="R20", value="20k", footprint="Resistor_SMD:R_0805_2012Metric")
    r21 = Component("Device:R", ref="R21", value="10k", footprint="Resistor_SMD:R_0805_2012Metric")
    c5 = Component("Device:C", ref="C5", value="100nF", footprint="Capacitor_SMD:C_0805_2012Metric")
    r20[1] += vw_pin17
    r20[2] += adc
    r21[1] += adc
    r21[2] += gnd
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    c5[2] += gnd


def throttle_switches(gnd, gp_idle, vw_pin11):
    """Corrected per the user's own hands-on HiL notes (F60 idle switch: 'Pin 6
    Masse und Pin 11'): VW-6 is NOT a second switch contact, it's the sensor/
    idle-switch common ground (wired straight to GND in main_circuit) -- there is
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    r19[1] += gp_idle
    r19[2] += gnd
    q5["S"] += gnd
    q5["D"] += vw_pin11


def dac_analog_sim(vcc_3v3, gnd, sda, scl, vw_pin9, vw_pin10, vw_pin21, vw_pin2,
                   gp_conn_air, gp_conn_water, gp_conn_lambda):
    """MCP4728 U2 (0x60): intake-air NTC, coolant NTC, LMM and lambda sim, each via
    a series resistor. The two NTC channels and the lambda channel additionally
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    # dac pin, series R, Rref, VW target, connect-enable GPIO (None = hard-wired),
    # switch ref, IN-pullup ref
    chans = [
        ("VOUTA", "220R", "R2", vw_pin9,  gp_conn_air,    "U6", "R22"),
        ("VOUTB", "220R", "R3", vw_pin10, gp_conn_water,  "U7", "R23"),
        ("VOUTC", "220R", "R4", vw_pin21, None,           None, None),
        ("VOUTD", "1k",   "R5", vw_pin2,  gp_conn_lambda, "U8", "R24"),
    ]
    for dac_pin, rval, rref, vw_net, gp_conn, swref, rpuref in chans:
        r = Component("Device:R", ref=rref, value=rval,
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        rpu[2] += vcc_3v3


def crank_driver(gpio_crank, gnd, ecu_12v, vw_pin18):
    """Q1 open-drain crank/Hallgeber signal driver, RPU1 pull-up to +12V_ECU.
    VW-18 confirmed (not VW-8) by the user's own working HiL notes: the crank
    square wave needs >=8-10V amplitude (5V is not enough) -- consistent with
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    rg1[1] += gpio_crank
    rg1[2] += q1["G"]
    q1["S"] += gnd
    q1["D"] += vw_pin18
    rpu1[1] += vw_pin18
    rpu1[2] += ecu_12v


def edge_capture(vcc_3v3, gpio_ignition, gpio_injector, vw_pin25, vw_pin12):
    """Ignition/injector edge capture: pull-up to Pico's own 3V3, series ESD guard."""
    r8 = Component("Device:R", ref="R8", value="10k", footprint="Resistor_SMD:R_0805_2012Metric")
    r9 = Component("Device:R", ref="R9", value="330R", footprint="Resistor_SMD:R_0805_2012Metric")
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    r11 = Component("Device:R", ref="R11", value="330R", footprint="Resistor_SMD:R_0805_2012Metric")

    r8[1] += vcc_3v3
    r8[2] += vw_pin25
    r9[1] += vw_pin25
    r9[2] += gpio_ignition

    r10[1] += vcc_3v3
    r10[2] += vw_pin12
    r11[1] += vw_pin12
    r11[2] += gpio_injector


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    pins via a short external pigtail -- clipped/soldered onto both pads, not
    a proper connector housing. A 2-pin JST here would be nicer, but this
    corner of the board is criss-crossed with existing traces on both layers
    (+12V_ECU_SW, VW_PIN10/11/12, GP8/GP9/GP13/GP26 all thread through here at
    various points); every placement tried for a through-hole 2-pin connector
    shorted a different existing net. Two bare test pads (TestPoint_Pad_D1.5mm,
    same as the original TP1) are small enough to actually fit."""
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    sda = Net("I2C_SDA")
    scl = Net("I2C_SCL")

    vw_pin2 = Net("VW_PIN2")
    vw_pin9 = Net("VW_PIN9")
    vw_pin10 = Net("VW_PIN10")
    vw_pin12 = Net("VW_PIN12")
    vw_pin18 = Net("VW_PIN18")
    vw_pin21 = Net("VW_PIN21")
    vw_pin25 = Net("VW_PIN25")

    gp_crank = Net("GP2_CRANK")
    gp_ignition = Net("GP14_IGN_CAPTURE")
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    gp_conn_water = Net("GP9_WATERTEMP_CONNECT")
    gp_conn_lambda = Net("GP11_LAMBDA_CONNECT")
    afm_ref_adc = Net("GP26_AFM_REF_ADC")
    vw_pin11 = Net("VW_PIN11")
    vw_pin17 = Net("VW_PIN17")

    # CONN_VW: 15-pos 10A/pin 5mm screw terminal block, one terminal per VW harness
    # pin the bench touches. Addressed by harness name; the symbol numbers its pads
    # 1..15 to match the footprint.
    j0 = Component("Custom_Digifant2:CONN_VW", ref="J0", value="VW ECU HARNESS",
                    footprint="TerminalBlock:TerminalBlock_MaiXu_MX126-5.0-15P_1x15_P5.00mm")
    j0["VW-2"] += vw_pin2
    j0["VW-6"] += gnd          # sensor/idle-switch common ground (confirmed by user's HiL notes)
    j0["VW-9"] += vw_pin9
    j0["VW-10"] += vw_pin10
    j0["VW-11"] += vw_pin11    # idle switch (single contact, pulled to VW-6/GND when idle)
    j0["VW-12"] += vw_pin12
    j0["VW-13"] += gnd
    j0["VW-14"] += ecu_sw
    j0["VW-17"] += vw_pin17    # airflow-pot reference (sensed only)
    j0["VW-18"] += vw_pin18
    j0["VW-19"] += gnd
    j0["VW-21"] += vw_pin21
    j0["VW-22"] += ecu_sw  # idle valve drive; switched rail (was direct +12V_ECU)
    vw_pin23_valve_return = Net("VW_PIN23_VALVE_RETURN")
    j0["VW-23"] += vw_pin23_valve_return
    j0["VW-25"] += vw_pin25

    power_section(vin_12v, gnd, ecu_12v, ecu_sw)
    ecu_power_switch(ecu_12v, ecu_sw, gnd, gp_ecu_en)
    ecu_current_sense(Net("+12V_POST_D1"), ecu_12v, gnd, vcc_3v3, sda, scl)
    valve_return_sense = Net("VALVE_RETURN_SENSE")  # J2 side of RS2, before the shunt
    idle_valve(ecu_sw, valve_return_sense, vw_pin23_valve_return, gnd, vcc_3v3, sda, scl)
    dac_analog_sim(vcc_3v3, gnd, sda, scl, vw_pin9, vw_pin10, vw_pin21, vw_pin2,
                   gp_conn_air, gp_conn_water, gp_conn_lambda)
    afm_ref_sense(vw_pin17, gnd, afm_ref_adc)
    throttle_switches(gnd, gp_thr_idle, vw_pin11)
    crank_driver(gp_crank, gnd, ecu_sw, vw_pin18)
    edge_capture(vcc_3v3, gp_ignition, gp_injector, vw_pin25, vw_pin12)
    knock_sim(vcc_3v3, gnd, gp_spi_sck, gp_spi_mosi, gp_spi_cs)
    operator_ui(vcc_3v3, gnd, sda, scl, gp_btn_menu, gp_btn_minus, gp_btn_plus)
    debug_test_points(gp_crank, gp_thr_idle, gp_ignition, gp_injector,
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    # 3V3_EN (weak internal pull-up per datasheet), VBUS/VSYS (module is powered via
    # its own USB connection to the PC, not from this board), SWCLK/SWDIO (no SWD
    # debug probe planned) are all intentionally left NC, same convention as above.
    u5["GPIO2"] += gp_crank
    u5["GPIO6"] += gp_thr_idle
    # GPIO7 free (was the 2nd throttle-switch driver; VW-6 turned out to be
    # ground, not a 2nd switch contact -- see throttle_switches()).
    u5["GPIO8"] += gp_conn_air
    u5["GPIO9"] += gp_conn_water
    u5["GPIO11"] += gp_conn_lambda
    u5["GPIO10"] += gp_led_data   # SK6812 (GP12 free)
    u5["GPIO13"] += gp_ecu_en
    u5["GPIO26_ADC0"] += afm_ref_adc
    u5["GPIO4"] += sda
    u5["GPIO5"] += scl
    u5["GPIO14"] += gp_ignition
    u5["GPIO15"] += gp_injector
    u5["GPIO16"] += gp_spi_cs
    u5["GPIO18"] += gp_spi_sck
    u5["GPIO19"] += gp_spi_mosi
    u5["GPIO20"] += gp_btn_menu
    u5["GPIO21"] += gp_btn_minus
    u5["GPIO22"] += gp_btn_plus


if __name__ == "__main__":
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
